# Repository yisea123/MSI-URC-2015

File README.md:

MSI-URC-2015
============
* Clone the repository
* Run gazebo.bash from On-Board if gazebo/ROS/DEM not installed
* Run configure.bash once if cloning to a new place or for first time
* Restart the terminal and type '@urc'

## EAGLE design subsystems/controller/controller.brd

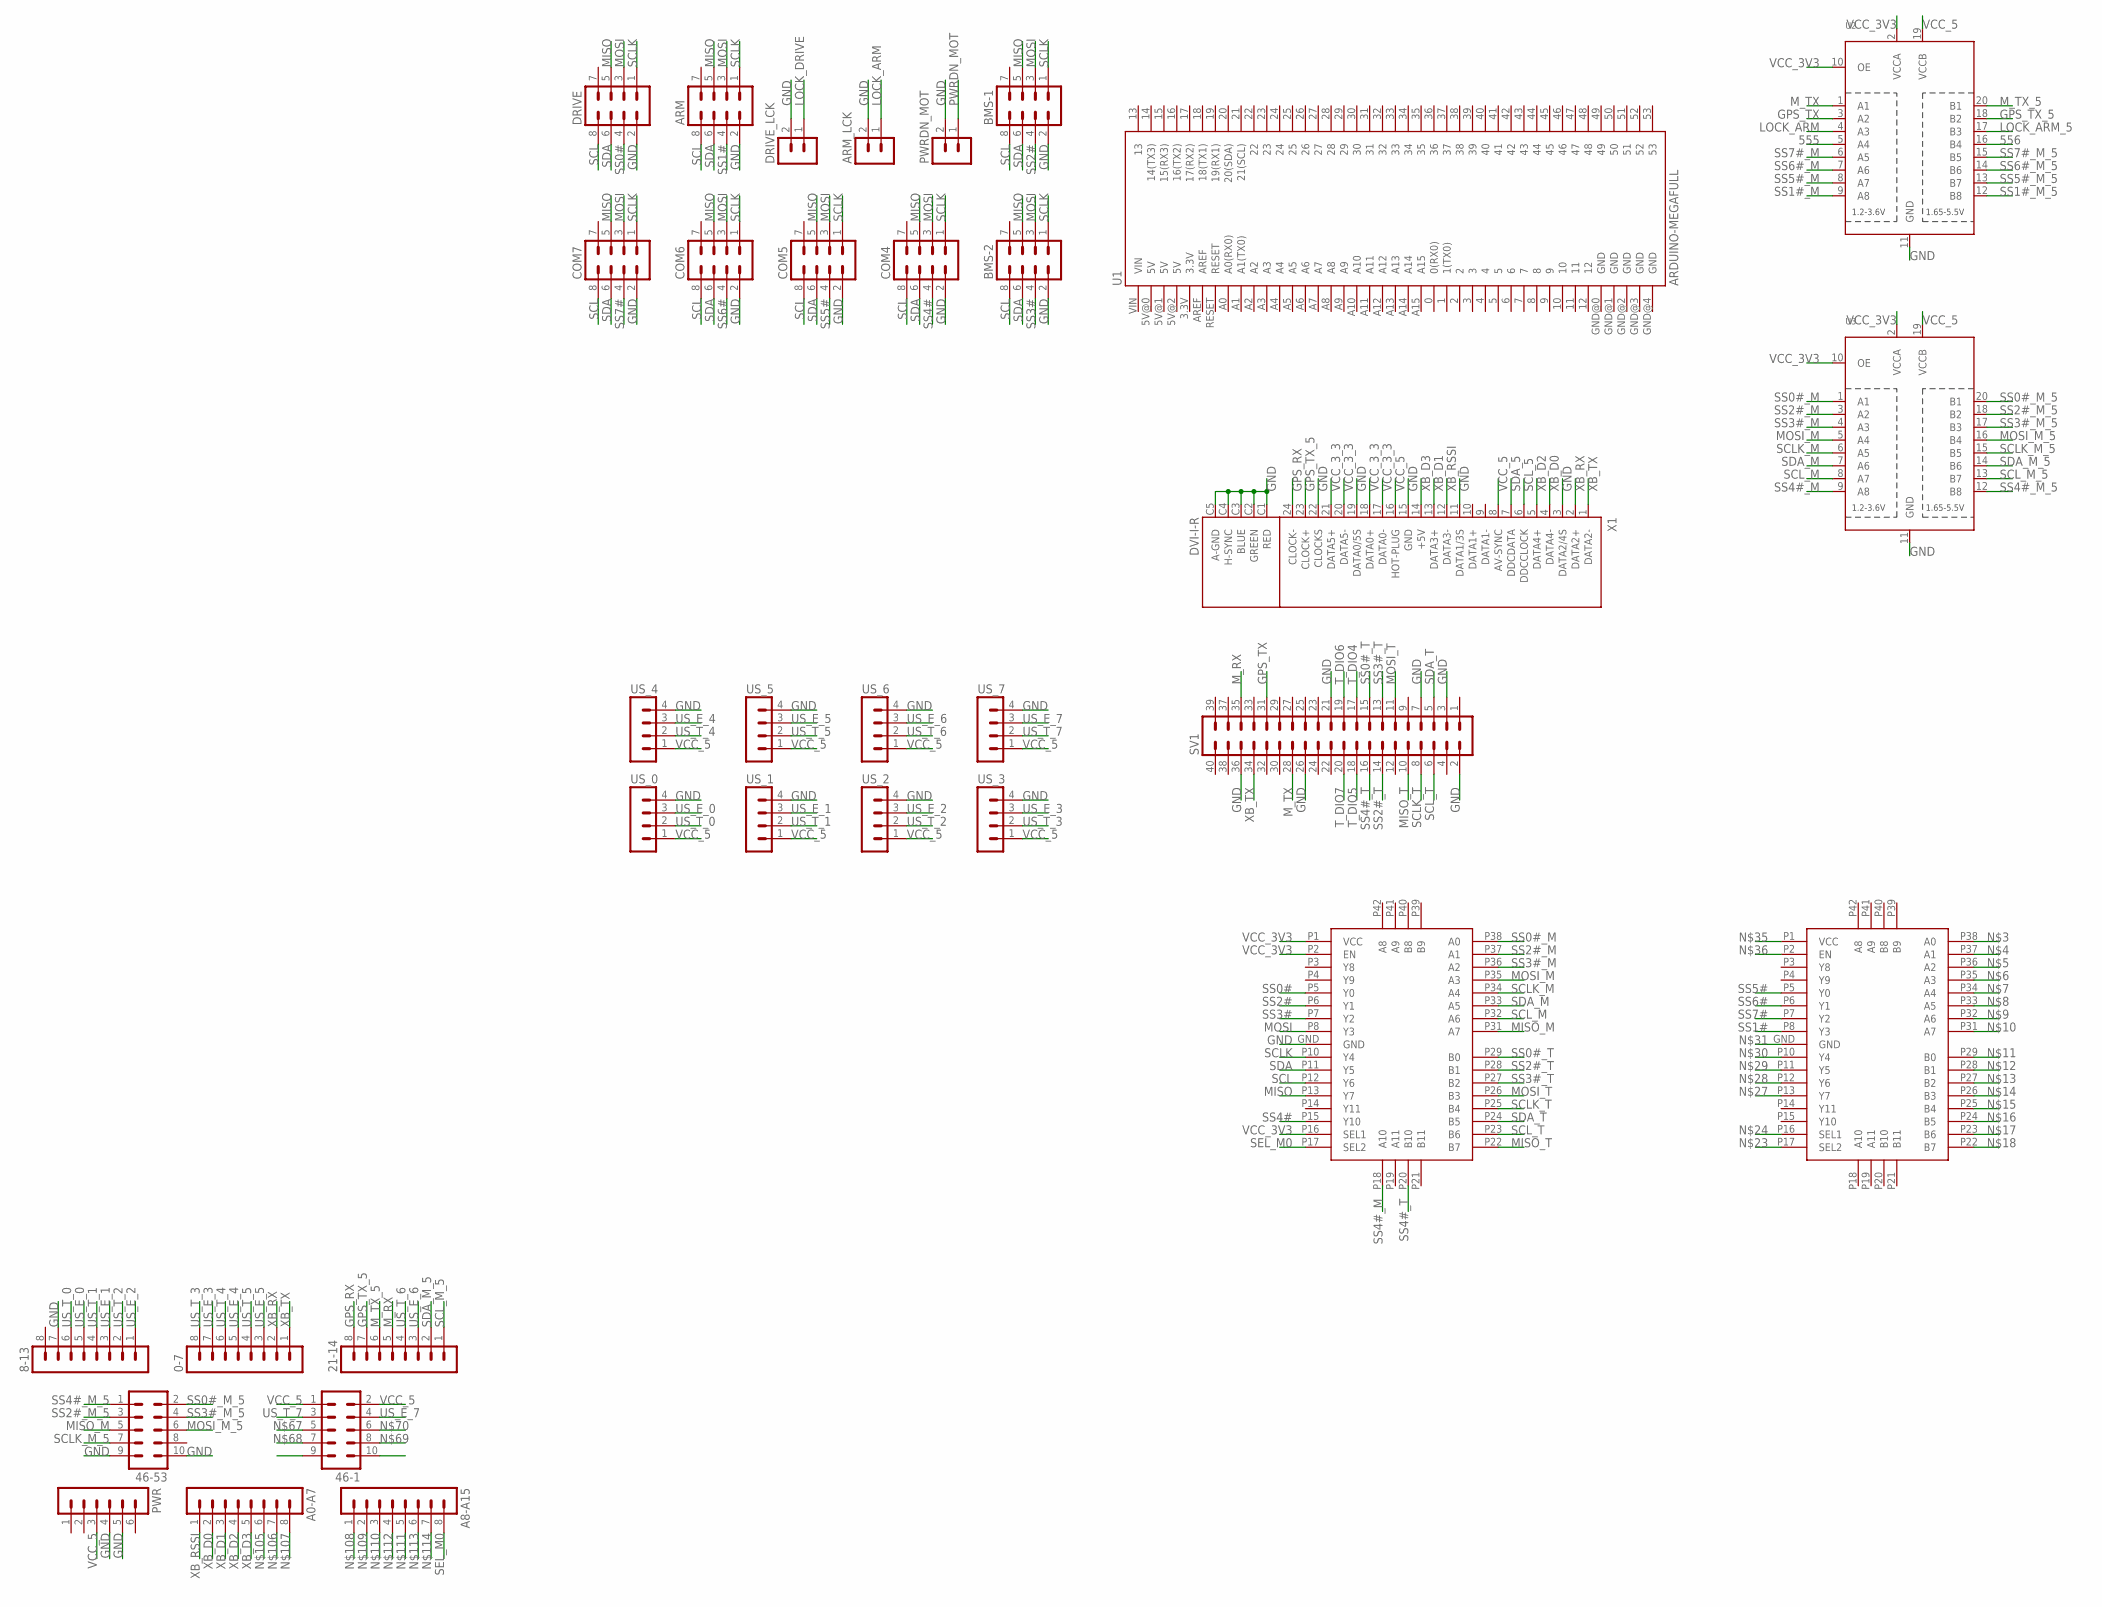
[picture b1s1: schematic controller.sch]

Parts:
0-7, 8-13, 21-14: MA08-1
46-1, 46-53: MA05-2
A0-A7, A8-A15: MA08-1
ARM: MA04-2
ARM_LCK: MA02-1
BMS-1, BMS-2: MA04-2
COM4, COM5, COM6, COM7: MA04-2
DRIVE: MA04-2
DRIVE_LCK: MA02-1
PWR: MA06-1
PWRDN_MOT: MA02-1
SV1: MA20-2
U1: ARDUINO-MEGAFULL; ARDUINO_MEGA
U2, U3: TXB0108PWR; TSSOP20
U$5, U$6: TS3DV642RUA; R-PWQFN-N42
US_0, US_1, US_2, US_3, US_4, US_5, US_6, US_7: MA04-1
X1: DVI-I-R

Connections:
555: U2.5 (A4)
556: U2.16 (B4)
AGND: X1.C6 (AGND)
GND: 8-13.7, 46-53.9, 46-53.10, ARM.2, ARM_LCK.2, BMS-1.2, BMS-2.2, COM4.2, COM5.2, COM6.2, COM7.2, DRIVE.2, DRIVE_LCK.2, PWR.4, PWR.5, PWRDN_MOT.2, SV1.2, SV1.3, SV1.7, SV1.21, SV1.26, SV1.36, U2.11 (GND), U3.11 (GND), U$5.GND, US_0.4, US_1.4, US_2.4, US_3.4, US_4.4, US_5.4, US_6.4, US_7.4, X1.3 (DATA2/4S), X1.11 (DATA1/3S), X1.15 (GND), X1.19 (DATA0/5S), X1.22 (CLOCKS), X1.C1 (RED), X1.C2 (GREEN), X1.C3 (BLUE), X1.C4 (H-SYNC), X1.C5 (A-GND)
GPS_RX: 21-14.8, X1.24 (CLOCK-)
GPS_TX: SV1.31, U2.3 (A2)
GPS_TX_5: 21-14.7, U2.18 (B2), X1.23 (CLOCK+)
LOCK_ARM: ARM_LCK.1, U2.4 (A3)
LOCK_ARM_5: U2.17 (B3)
LOCK_DRIVE: DRIVE_LCK.1
MISO: ARM.5, BMS-1.5, BMS-2.5, COM4.5, COM5.5, COM6.5, COM7.5, DRIVE.5, U$5.P13 (Y7)
MISO_M: 46-53.5, U$5.P31 (A7)
MISO_T: SV1.10, U$5.P22 (B7)
MOSI: ARM.3, BMS-1.3, BMS-2.3, COM4.3, COM5.3, COM6.3, COM7.3, DRIVE.3, U$5.P8 (Y3)
MOSI_M: U3.5 (A4), U$5.P35 (A3)
MOSI_M_5: 46-53.6, U3.16 (B4)
MOSI_T: SV1.11, U$5.P26 (B3)
M_RX: 21-14.5, SV1.35
M_TX: SV1.28, U2.1 (A1)
M_TX_5: 21-14.6, U2.20 (B1)
PWRDN_MOT: PWRDN_MOT.1
SCL: ARM.8, BMS-1.8, BMS-2.8, COM4.8, COM5.8, COM6.8, COM7.8, DRIVE.8, U$5.P12 (Y6)
SCLK: ARM.1, BMS-1.1, BMS-2.1, COM4.1, COM5.1, COM6.1, COM7.1, DRIVE.1, U$5.P10 (Y4)
SCLK_M: U3.6 (A5), U$5.P34 (A4)
SCLK_M_5: 46-53.7, U3.15 (B5)
SCLK_T: SV1.8, U$5.P25 (B4)
SCL_5: X1.6 (DDCCLOCK)
SCL_M: U3.8 (A7), U$5.P32 (A6)
SCL_M_5: 21-14.1, U3.13 (B7)
SCL_T: SV1.6, U$5.P23 (B6)
SDA: ARM.6, BMS-1.6, BMS-2.6, COM4.6, COM5.6, COM6.6, COM7.6, DRIVE.6, U$5.P11 (Y5)
SDA_5: X1.7 (DDCDATA)
SDA_M: U3.7 (A6), U$5.P33 (A5)
SDA_M_5: 21-14.2, U3.14 (B6)
SDA_T: SV1.5, U$5.P24 (B5)
SEL_M0: A8-A15.8, U$5.P17 (SEL2)
SS0#: DRIVE.4, U$5.P5 (Y0)
SS0#_M: U3.1 (A1), U$5.P38 (A0)
SS0#_M_5: 46-53.2, U3.20 (B1)
SS0#_T: SV1.15, U$5.P29 (B0)
SS1#: ARM.4, U$6.P8 (Y3)
SS1#_M: U2.9 (A8)
SS1#_M_5: U2.12 (B8)
SS2#: BMS-1.4, U$5.P6 (Y1)
SS2#_M: U3.3 (A2), U$5.P37 (A1)
SS2#_M_5: 46-53.3, U3.18 (B2)
SS2#_T: SV1.14, U$5.P28 (B1)
SS3#: BMS-2.4, U$5.P7 (Y2)
SS3#_M: U3.4 (A3), U$5.P36 (A2)
SS3#_M_5: 46-53.4, U3.17 (B3)
SS3#_T: SV1.13, U$5.P27 (B2)
SS4#: COM4.4, U$5.P15 (Y10)
SS4#_M: U3.9 (A8), U$5.P18 (A10)
SS4#_M_5: 46-53.1, U3.12 (B8)
SS4#_T: SV1.16, U$5.P20 (B10)
SS5#: COM5.4, U$6.P5 (Y0)
SS5#_M: U2.8 (A7)
SS5#_M_5: U2.13 (B7)
SS6#: COM6.4, U$6.P6 (Y1)
SS6#_M: U2.7 (A6)
SS6#_M_5: U2.14 (B6)
SS7#: COM7.4, U$6.P7 (Y2)
SS7#_M: U2.6 (A5)
SS7#_M_5: U2.15 (B5)
T_DIO4: SV1.17
T_DIO5: SV1.18
T_DIO6: SV1.19
T_DIO7: SV1.20
US_E_0: 8-13.5, US_0.3
US_E_1: 8-13.3, US_1.3
US_E_2: 8-13.1, US_2.3
US_E_3: 0-7.7, US_3.3
US_E_4: 0-7.5, US_4.3
US_E_5: 0-7.3, US_5.3
US_E_6: 21-14.3, US_6.3
US_E_7: 46-1.4, US_7.3
US_T_0: 8-13.6, US_0.2
US_T_1: 8-13.4, US_1.2
US_T_2: 8-13.2, US_2.2
US_T_3: 0-7.8, US_3.2
US_T_4: 0-7.6, US_4.2
US_T_5: 0-7.4, US_5.2
US_T_6: 21-14.4, US_6.2
US_T_7: 46-1.3, US_7.2
VCC_3V3: U2.2 (VCCA), U2.10 (OE), U3.2 (VCCA), U3.10 (OE), U$5.P1 (VCC), U$5.P2 (EN), U$5.P16 (SEL1)
VCC_3_3: X1.17 (DATA0-), X1.18 (DATA0+), X1.20 (DATA5-), X1.21 (DATA5+)
VCC_5: 46-1.1, 46-1.2, PWR.3, U2.19 (VCCB), U3.19 (VCCB), US_0.1, US_1.1, US_2.1, US_3.1, US_4.1, US_5.1, US_6.1, US_7.1, X1.8 (AV-SYNC), X1.16 (HOT-PLUG)
XB_D0: A0-A7.2, X1.4 (DATA4-)
XB_D1: A0-A7.3, X1.13 (DATA3+)
XB_D2: A0-A7.4, X1.5 (DATA4+)
XB_D3: A0-A7.5, X1.14 (+5V)
XB_RSSI: A0-A7.1, X1.12 (DATA3-)
XB_RX: 0-7.2, X1.2 (DATA2+)
XB_TX: 0-7.1, SV1.34, X1.1 (DATA2-)

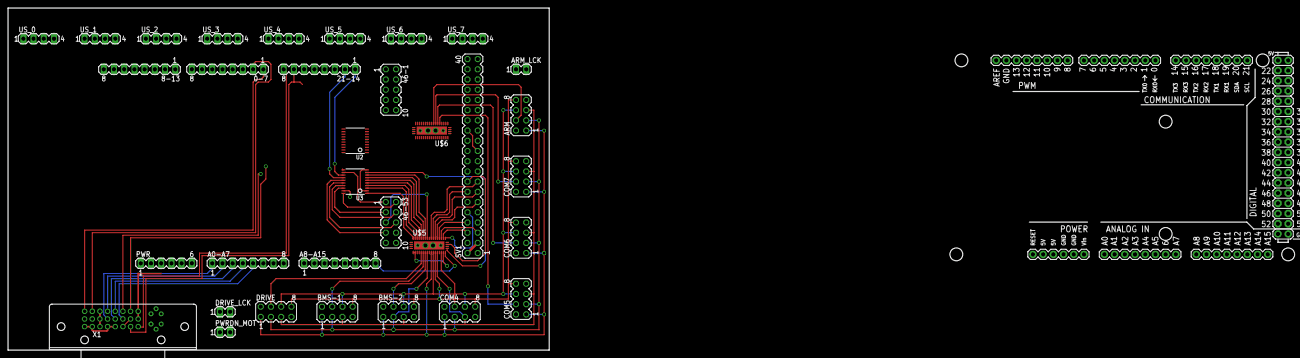
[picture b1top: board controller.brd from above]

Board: 2 copper layers, 134.6 x 85.1 mm, 34 parts (0 on the bottom side), 74 nets.

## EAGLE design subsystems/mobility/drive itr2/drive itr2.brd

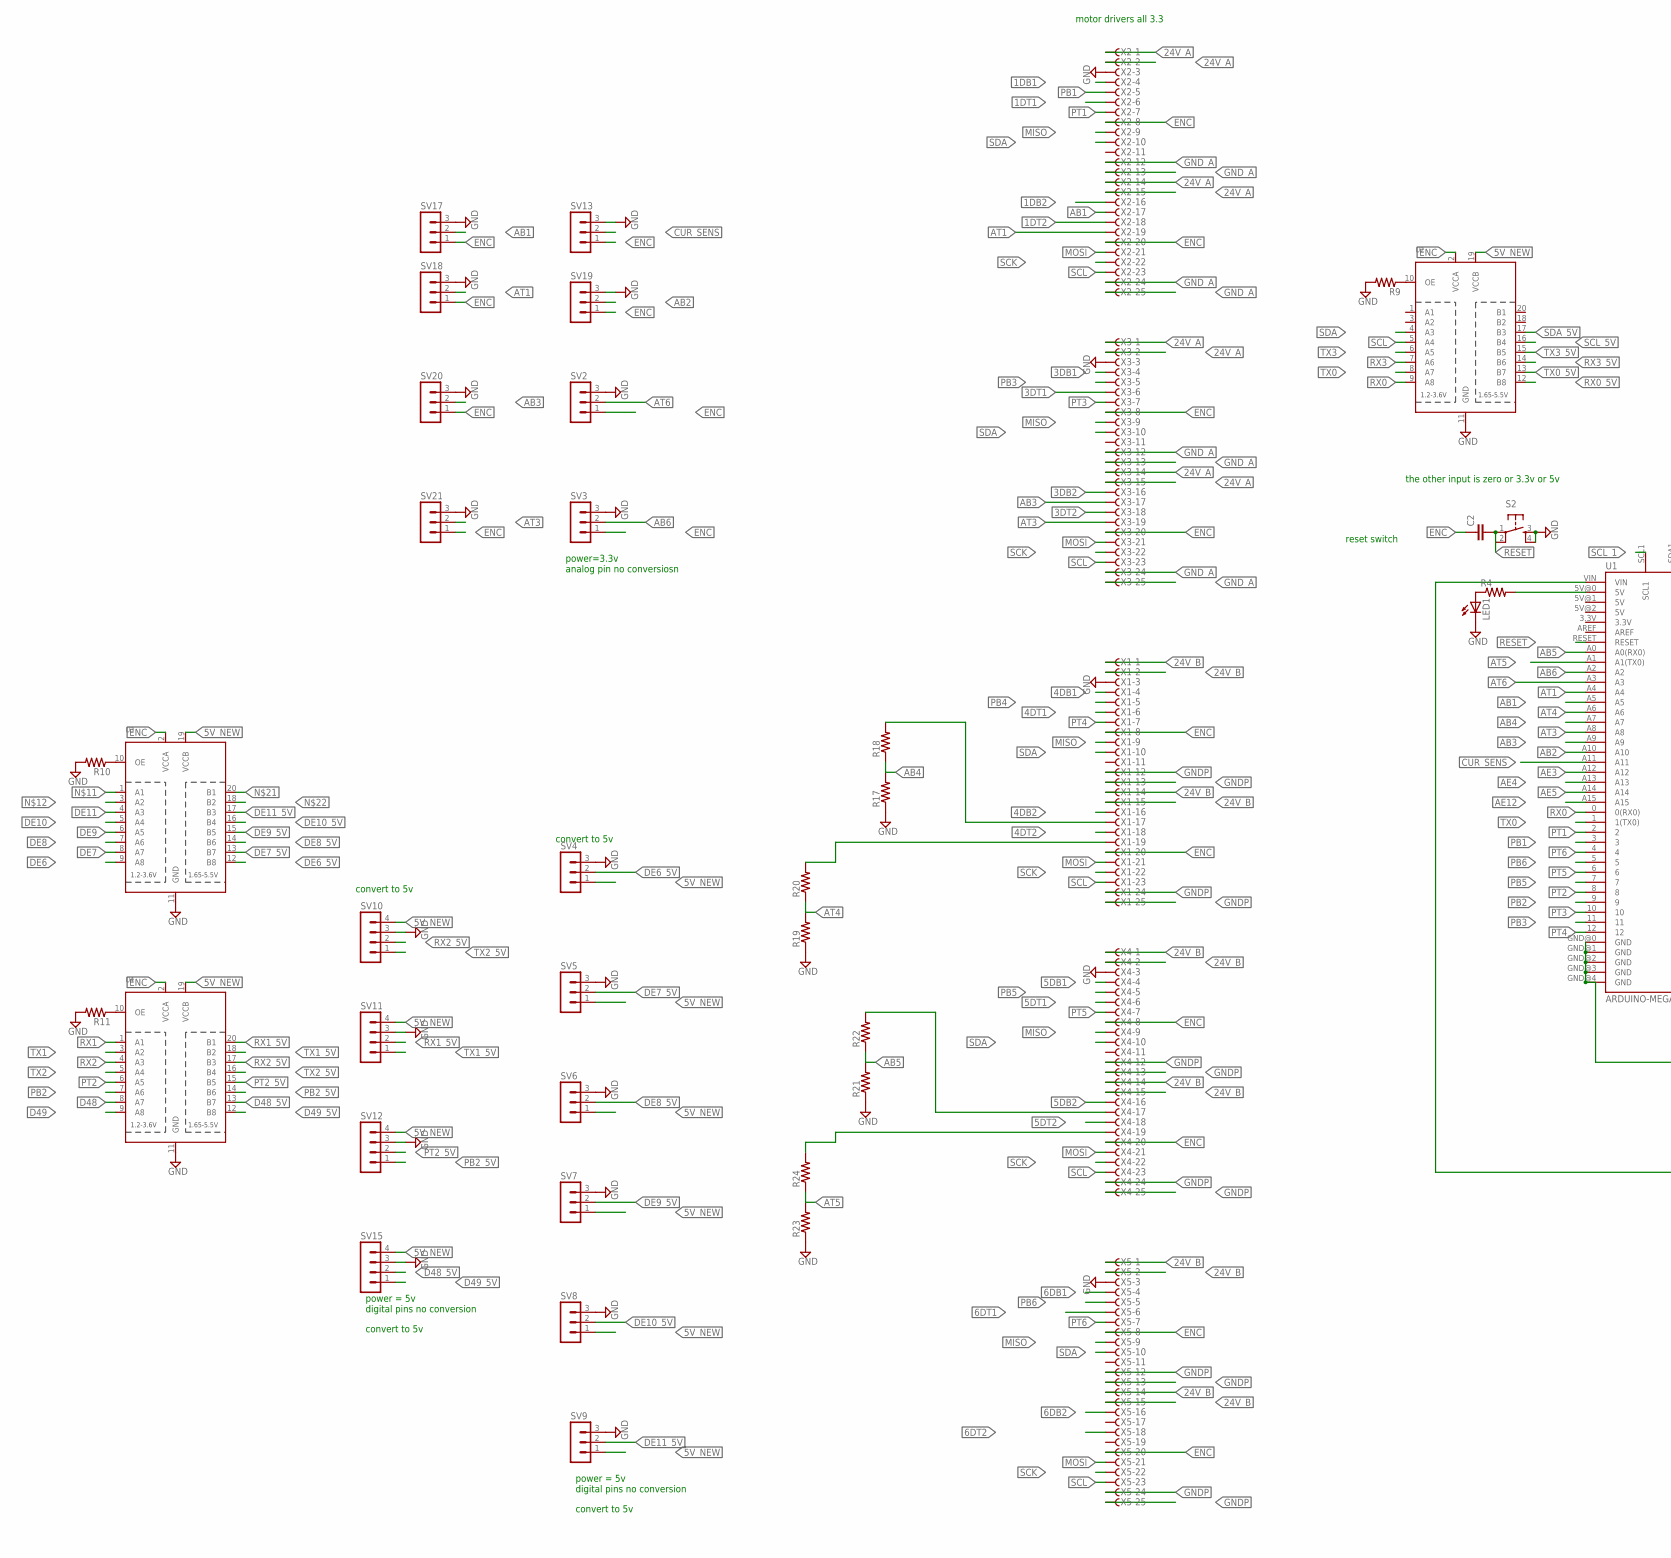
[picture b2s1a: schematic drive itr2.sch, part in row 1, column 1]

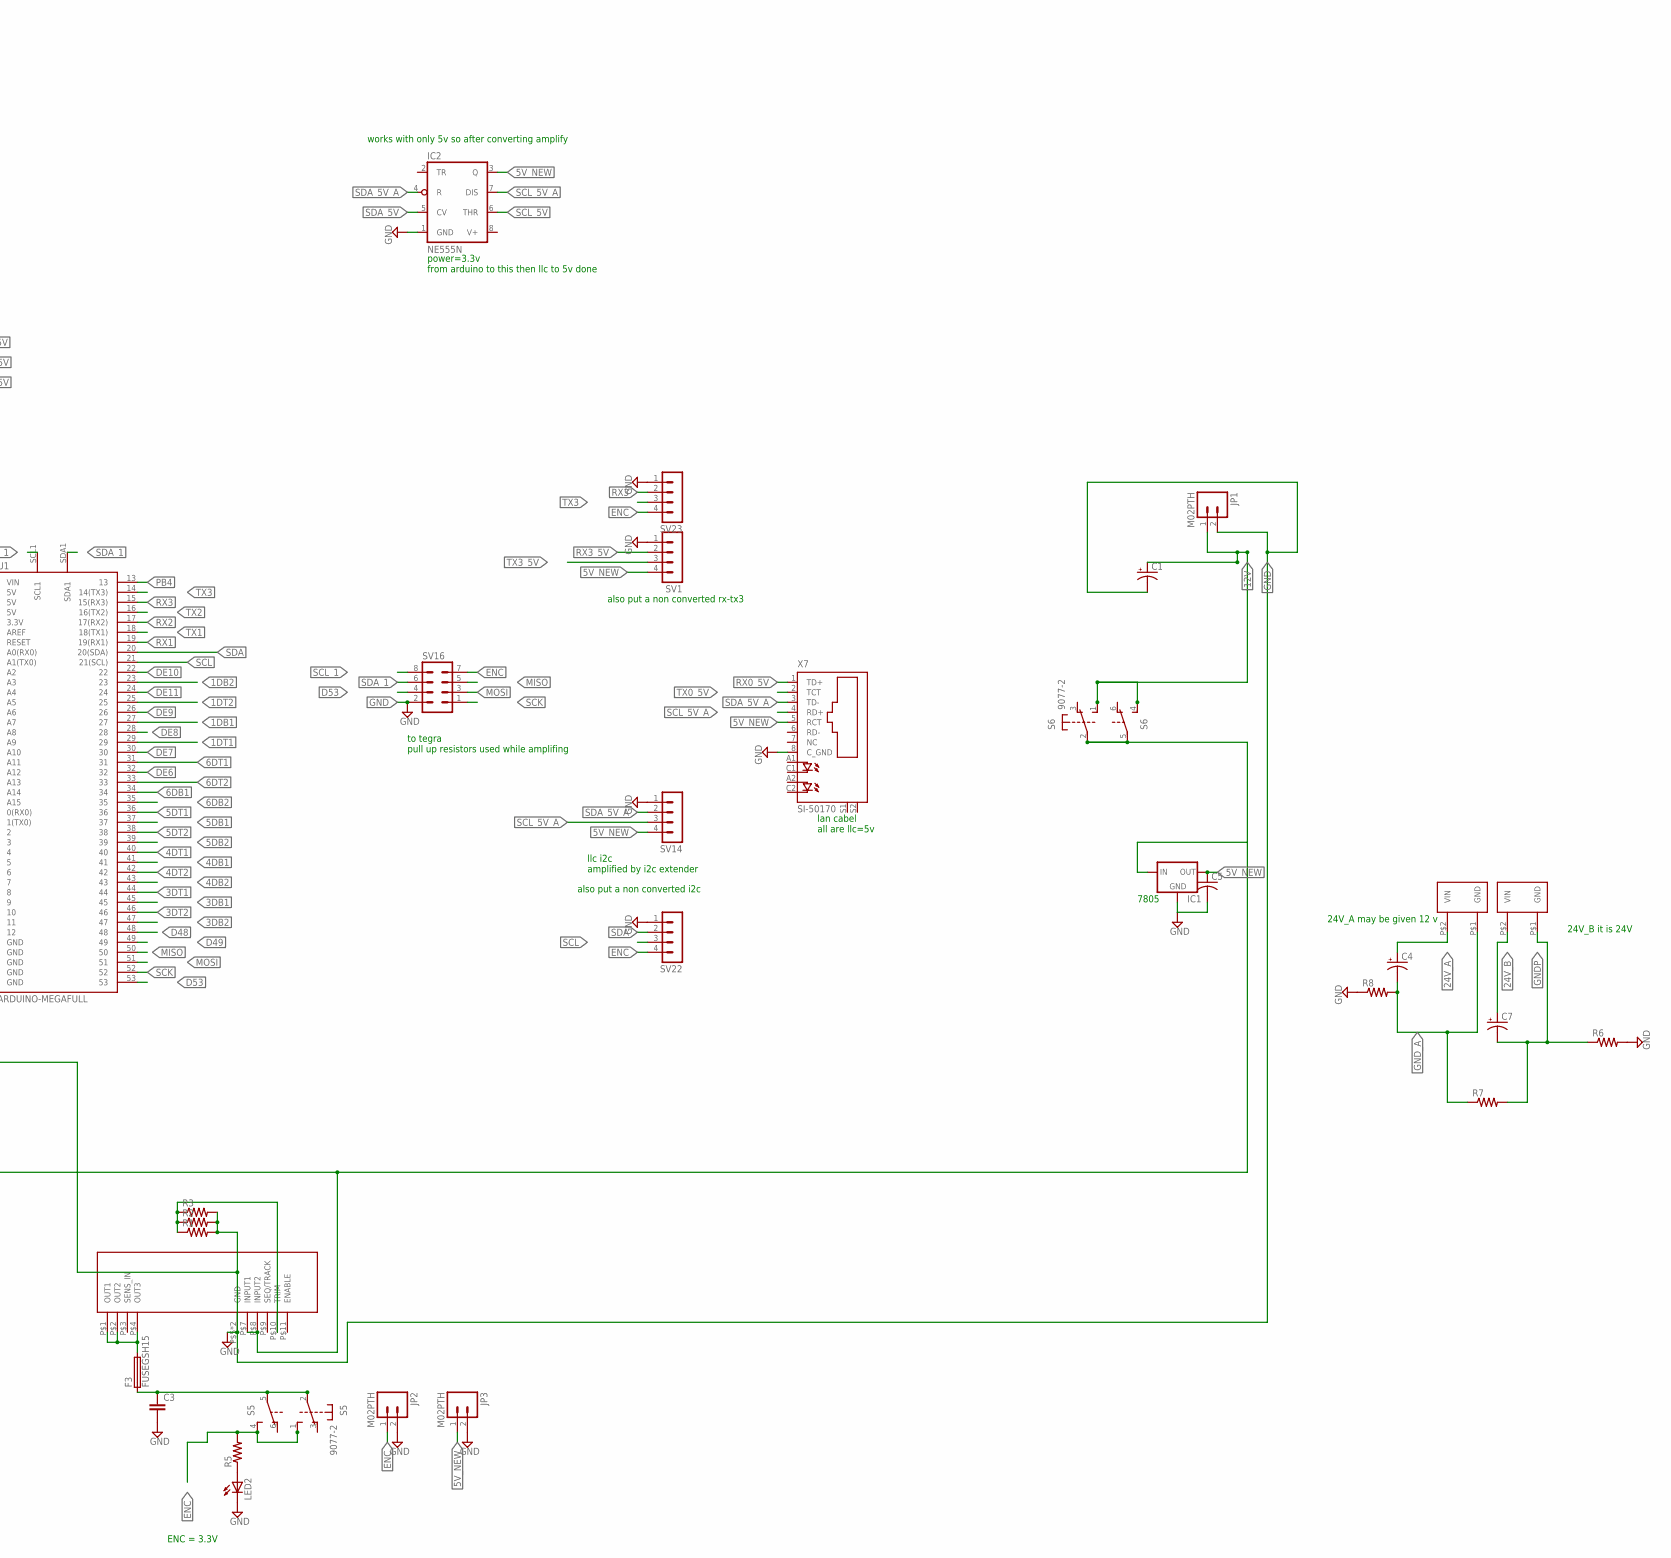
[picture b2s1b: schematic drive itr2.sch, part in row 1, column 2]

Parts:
C1, C4, C7: CPOL-USE2.5-5; E2,5-5
C2: C2,5-3; C2.5-3
C3: C2.5/2; C2.5-2
C5: C-US025-030X050; C025-030X050
F3: FUSEGSH15; GSH15
IC1: V_REG_78XX-TO-220; TO-220-ALT
IC2: NE555N; DIL08-ROUND
JP1, JP2, JP3: M02PTH; 1X02
LED1, LED2: LED3MM
R1, R2, R3, R4, R5, R6, R7, R8, R9, R10, R11, R17, R18, R19, R20, R21, R22, R23, R24: R-US_0207/10; 0207/10
S2: TAC_SWITCHSMD; TACTILE-SWITCH-SMD
S5, S6: 9077-2
SV1, SV10, SV11, SV12, SV14, SV15, SV22, SV23: MA04-1
SV2, SV3, SV4, SV5, SV6, SV7, SV8, SV9, SV13, SV17, SV18, SV19, SV20, SV21: MA03-1
SV16: MA04-2
U1: ARDUINO-MEGAFULL; ARDUINO_MEGA
U2, U3, U4: TXB0108PWR; TSSOP20
U$7: VREG-MURATA; VREG
U$8, U$9: POW_HOLE
X1, X2, X3, X4, X5: F25HPS; F25HP
X7: SI-50170

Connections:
1DB1: U1.27, X2.4
1DB2: U1.23, X2.16
1DT1: U1.29, X2.6
1DT2: U1.25, X2.18
3DB1: U1.45, X3.4
3DB2: U1.47, X3.16
3DT1: U1.44, X3.6
3DT2: U1.46, X3.18
4DB1: U1.41, X1.4
4DB2: U1.43, X1.16
4DT1: U1.40, X1.6
4DT2: U1.42, X1.18
5DB1: U1.37, X4.4
5DB2: U1.39, X4.16
5DT1: U1.36, X4.6
5DT2: U1.38, X4.18
5V_NEW: C5.1, IC1.OUT, IC2.3 (Q), JP3.1, SV1.4, SV4.1, SV5.1, SV6.1, SV7.1, SV8.1, SV9.1, SV10.4, SV11.4, SV12.4, SV14.4, SV15.4, U2.19 (VCCB), U3.19 (VCCB), U4.19 (VCCB), X7.5 (RCT)
6DB1: U1.34, X5.4
6DB2: U1.35, X5.16
6DT1: U1.31, X5.6
6DT2: U1.33, X5.18
12V: C1.+, JP1.1, S6.1 (S), S6.4 (S)
24V_A: C4.+, U$9.P$2 (VIN), X2.1, X2.2, X2.14, X2.15, X3.1, X3.2, X3.14, X3.15
24V_B: C7.+, U$8.P$2 (VIN), X1.1, X1.2, X1.14, X1.15, X4.1, X4.2, X4.14, X4.15, X5.1, X5.2, X5.14, X5.15
AB1: SV17.2, U1.A5, X2.17
AB2: SV19.2, U1.A10
AB3: SV20.2, U1.A9, X3.17
AB4: R17.2, R18.1, U1.A7
AB5: R21.2, R22.1, U1.A0 (A0(RX0))
AB6: SV3.2, U1.A2
AE3: U1.A12
AE4: U1.A13
AE5: U1.A14
AE12: U1.A15
AT1: SV18.2, U1.A4
AT3: SV21.2, U1.A8, X3.19
AT4: R19.2, R20.1, U1.A6
AT5: R23.2, R24.1, U1.A1 (A1(TX0))
AT6: SV2.2, U1.A3
CONN: C3.1, F3.1, S5.2, S5.5
CUR_SENS: SV13.2, U1.A11
D48: U1.48, U4.8 (A7)
D48_5V: SV15.2, U4.13 (B7)
D49: U1.49, U4.9 (A8)
D49_5V: SV15.1, U4.12 (B8)
D53: SV16.4, U1.53
DE6: U1.32, U3.9 (A8)
DE6_5V: SV4.2, U3.12 (B8)
DE7: U1.30, U3.8 (A7)
DE7_5V: SV5.2, U3.13 (B7)
DE8: U1.28, U3.7 (A6)
DE8_5V: SV6.2, U3.14 (B6)
DE9: U1.26, U3.6 (A5)
DE9_5V: SV7.2, U3.15 (B5)
DE10: U1.22, U3.5 (A4)
DE10_5V: SV8.2, U3.16 (B4)
DE11: U1.24, U3.4 (A3)
DE11_5V: SV9.2, U3.17 (B3)
ENC: C2.1, JP2.1, R5.2, S5.1 (S), S5.4 (S), SV2.1, SV3.1, SV13.1, SV16.7, SV17.1, SV18.1, SV19.1, SV20.1, SV21.1, SV22.4, SV23.4, U2.2 (VCCA), U3.2 (VCCA), U4.2 (VCCA), X1.8, X1.20, X2.8, X2.20, X3.8, X3.20, X4.8, X4.20, X5.8, X5.20
GND: C1.-, C3.2, C5.2, IC1.GND, IC2.1 (GND), JP1.2, JP2.2, JP3.2, LED1.K (C), LED2.K (C), R1.2, R2.2, R3.2, R6.2, R8.1, R9.2, R10.2, R11.2, R17.1, R19.1, R21.1, R23.1, S2.3, S2.4, SV1.1, SV2.3, SV3.3, SV4.3, SV5.3, SV6.3, SV7.3, SV8.3, SV9.3, SV10.3, SV11.3, SV12.3, SV13.3, SV14.1, SV15.3, SV16.2, SV17.3, SV18.3, SV19.3, SV20.3, SV21.3, SV22.1, SV23.1, U1.GND@0 (GND), U1.GND@1 (GND), U1.GND@2 (GND), U1.GND@3 (GND), U1.GND@4 (GND), U2.11 (GND), U3.11 (GND), U4.11 (GND), U$7.P$5 (GND), U$7.P$6 (GND), X1.3, X2.3, X3.3, X4.3, X5.3, X7.8 (C_GND)
GNDP: C7.-, R6.1, R7.2, U$8.P$1 (GND), X1.12, X1.13, X1.24, X1.25, X4.12, X4.13, X4.24, X4.25, X5.12, X5.13, X5.24, X5.25
GND_A: C4.-, R7.1, R8.2, U$9.P$1 (GND), X2.12, X2.13, X2.24, X2.25, X3.12, X3.13, X3.24, X3.25
MISO: SV16.5, U1.50, X1.9, X2.9, X3.9, X4.9, X5.9
MOSI: SV16.3, U1.51, X1.21, X2.21, X3.21, X4.21, X5.21
unnamed: R9.1, U2.10 (OE)
unnamed: R10.1, U3.10 (OE)
unnamed: R11.1, U4.10 (OE)
unnamed: LED2.A, R5.1
unnamed: LED1.A, R4.1
unnamed: R4.2, U1.5V@0 (5V)
unnamed: F3.2, U$7.P$1 (OUT1), U$7.P$2 (OUT2), U$7.P$4 (OUT3)
unnamed: IC1.IN, S6.2, S6.5, U1.VIN, U$7.P$7 (INPUT1), U$7.P$8 (INPUT2)
unnamed: R18.2, X1.17
unnamed: R20.2, X1.19
unnamed: R22.2, X4.17
unnamed: R24.2, X4.19
unnamed: R1.1, R2.1, R3.1, U$7.P$10 (TRIM)
PB1: U1.3, X2.5
PB2: U1.9, U4.7 (A6)
PB2_5V: SV12.1, U4.14 (B6)
PB3: U1.11, X3.5
PB4: U1.13, X1.5
PB5: U1.7, X4.5
PB6: U1.5, X5.5
PT1: U1.2, X2.7
PT2: U1.8, U4.6 (A5)
PT2_5V: SV12.2, U4.15 (B5)
PT3: U1.10, X3.7
PT4: U1.12, X1.7
PT5: U1.6, X4.7
PT6: U1.4, X5.7
RESET: C2.2, S2.1, S2.2, U1.RESET
RX0: U1.0 (0(RX0)), U2.9 (A8)
RX0_5V: U2.12 (B8), X7.1 (TD+)
RX1: U1.19 (19(RX1)), U4.1 (A1)
RX1_5V: SV11.2, U4.20 (B1)
RX2: U1.17 (17(RX2)), U4.4 (A3)
RX2_5V: SV10.2, U4.17 (B3)
RX3: SV23.2, U1.15 (15(RX3)), U2.7 (A6)
RX3_5V: SV1.2, U2.14 (B6)
SCK: SV16.1, U1.52, X1.22, X2.22, X3.22, X4.22, X5.22
SCL: SV22.3, U1.21 (21(SCL)), U2.5 (A4), X1.23, X2.23, X3.23, X4.23, X5.23
SCL_1: SV16.8, U1.SCL1
SCL_5V: IC2.6 (THR), U2.16 (B4)
SCL_5V_A: IC2.7 (DIS), SV14.3, X7.4 (RD+)
SDA: SV22.2, U1.20 (20(SDA)), U2.4 (A3), X1.10, X2.10, X3.10, X4.10, X5.10
SDA_1: SV16.6, U1.SDA1
SDA_5V: IC2.5 (CV), U2.17 (B3)
SDA_5V_A: IC2.4 (R), SV14.2, X7.3 (TD-)
TX0: U1.1 (1(TX0)), U2.8 (A7)
TX0_5V: U2.13 (B7), X7.2 (TCT)
TX1: U1.18 (18(TX1)), U4.3 (A2)
TX1_5V: SV11.1, U4.18 (B2)
TX2: U1.16 (16(TX2)), U4.5 (A4)
TX2_5V: SV10.1, U4.16 (B4)
TX3: SV23.3, U1.14 (14(TX3)), U2.6 (A5)
TX3_5V: SV1.3, U2.15 (B5)
V+: IC2.8 (V+)

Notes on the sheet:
power = 5v digital pins no conversion
power=3.3v analog pin no conversiosn
power=3.3v from arduino to this then llc to 5v done
llc i2c amplified by i2c extender
lan cabel all are llc=5v
24V_A may be given 12 v
24V_B it is 24V
ENC = 3.3V
to tegra pull up resistors used while amplifing
reset switch
7805
the other input is zero or 3.3v or 5v
motor drivers all 3.3
works with only 5v so after converting amplify
also put a non converted rx-tx3
also put a non converted i2c
convert to 5v

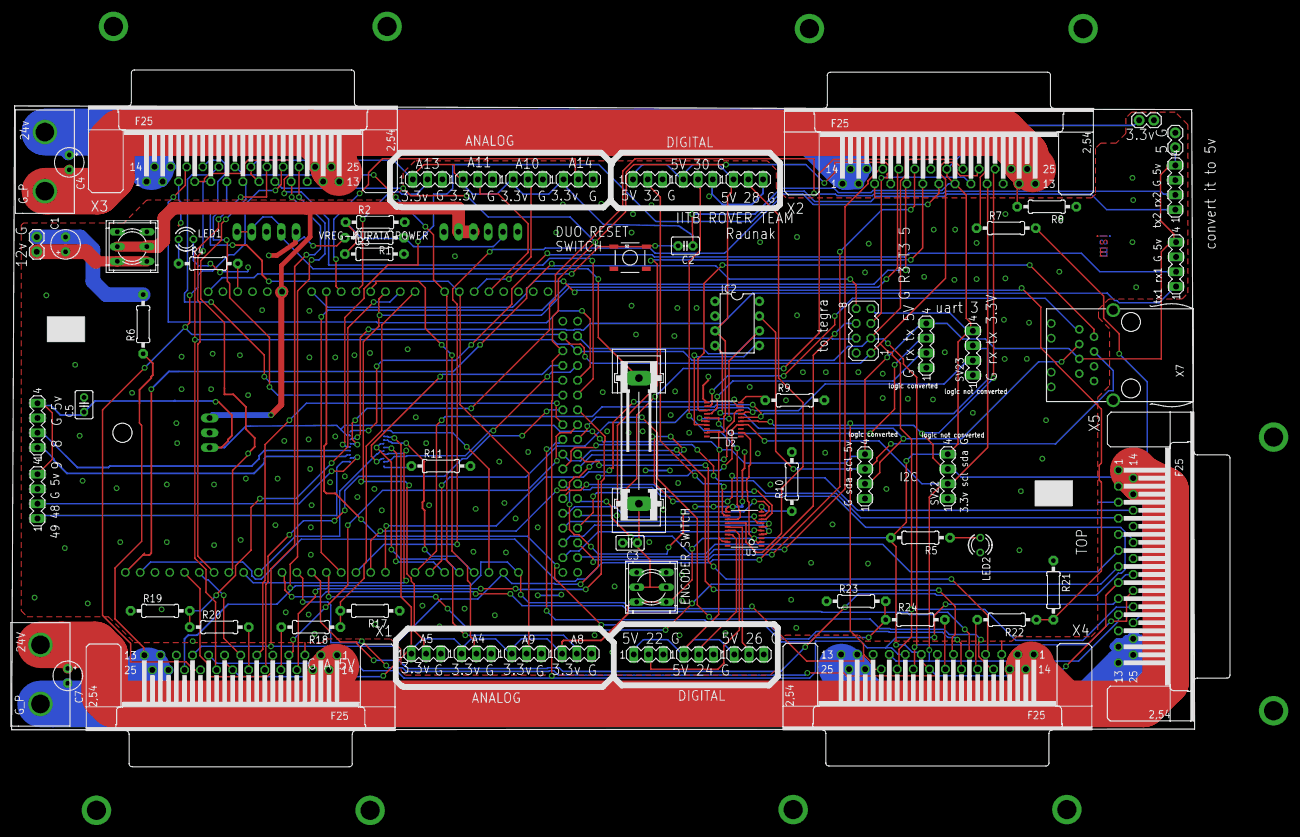
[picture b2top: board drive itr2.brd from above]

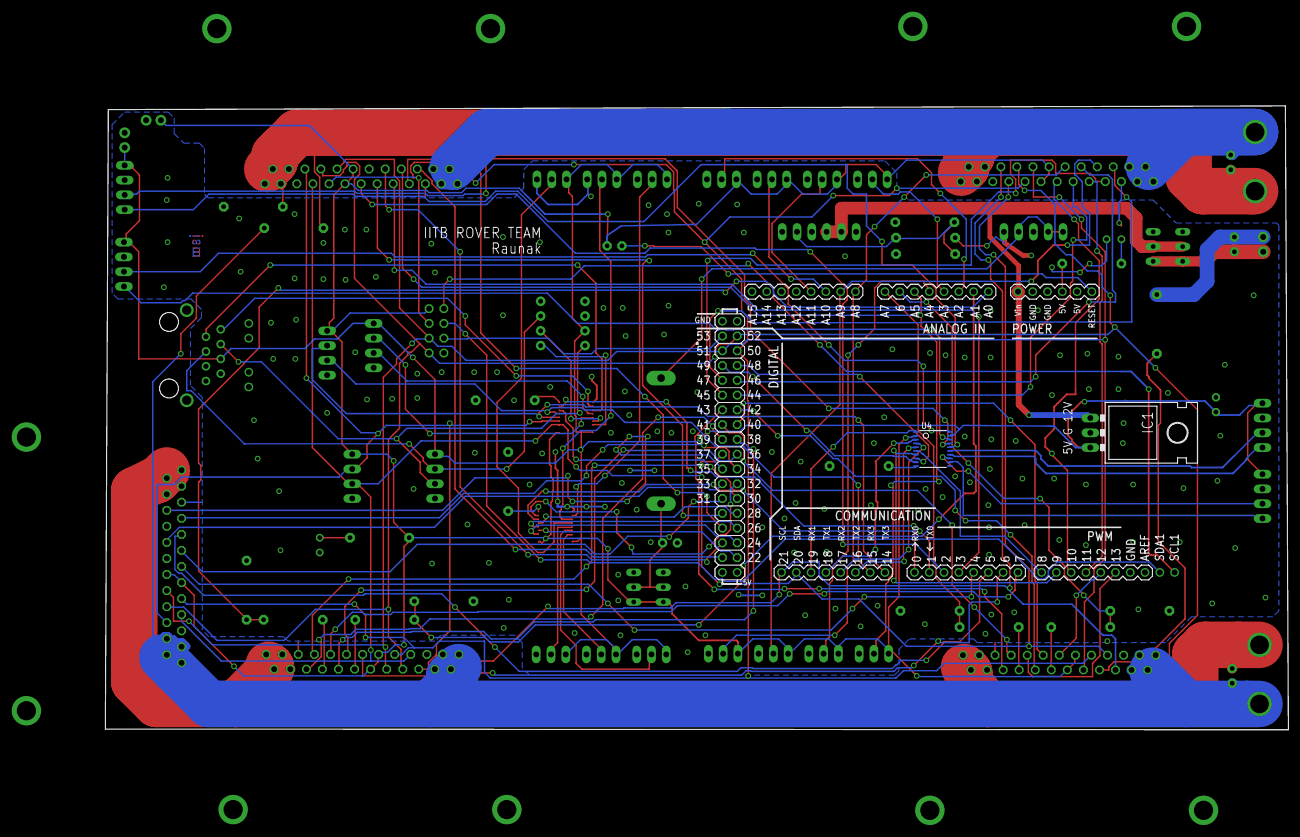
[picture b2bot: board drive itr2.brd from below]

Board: 2 copper layers, 203.3 x 107.2 mm, 74 parts (3 on the bottom side), 113 nets.

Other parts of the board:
U$1, U$2: MSI

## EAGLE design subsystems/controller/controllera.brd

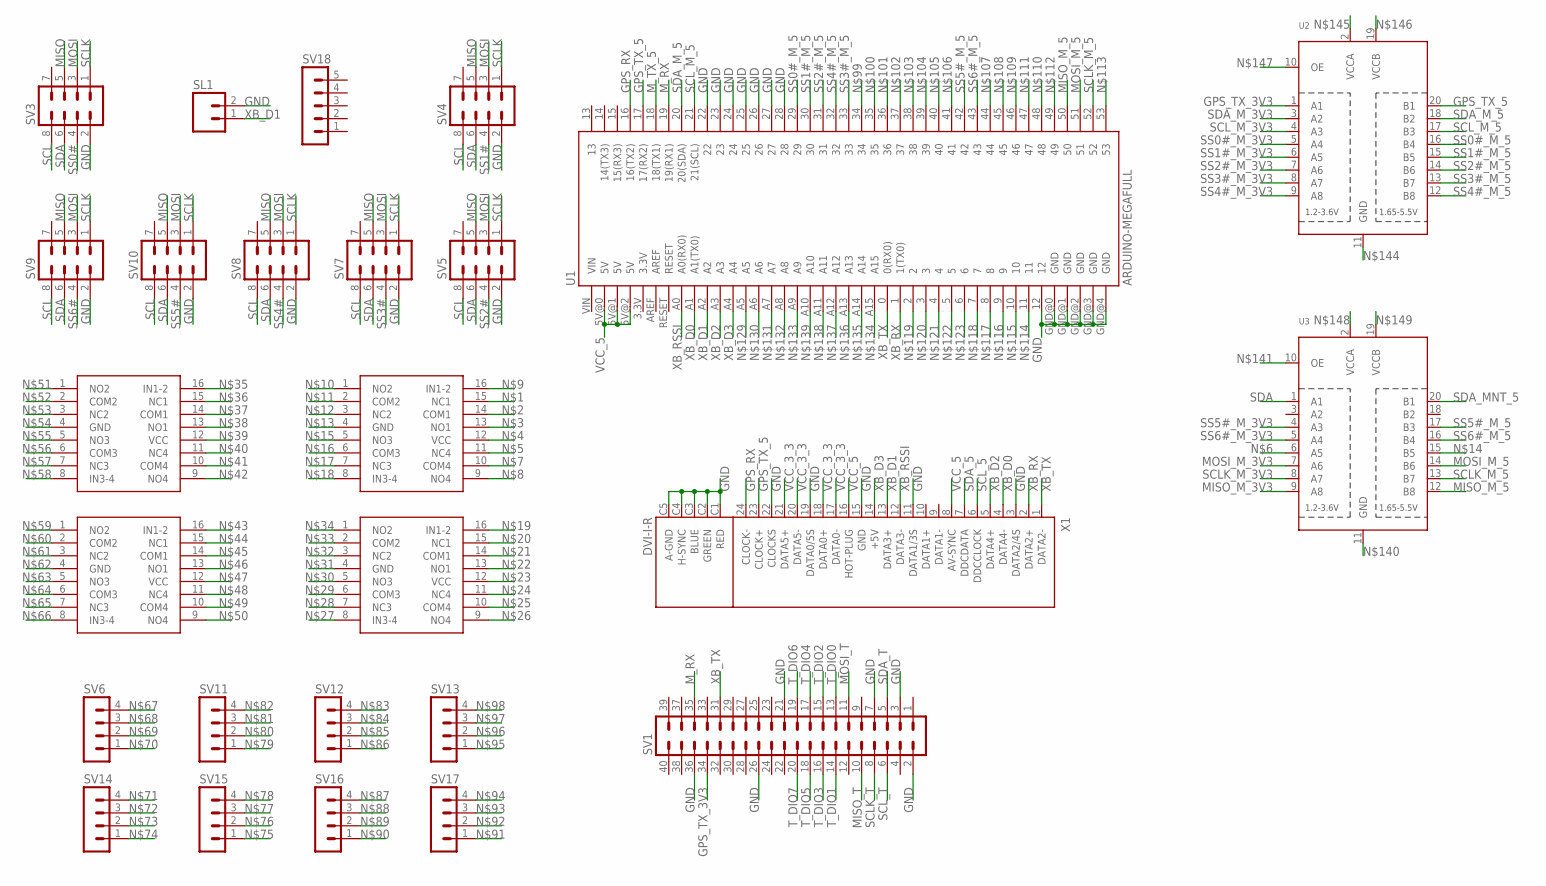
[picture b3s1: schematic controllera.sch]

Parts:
SL1: MA02; 02PA
SV1: MA20-2
SV3, SV4, SV5, SV7, SV8, SV9, SV10: MA04-2
SV6, SV11, SV12, SV13, SV14, SV15, SV16, SV17: MA04-1
SV18: MA05-1
U1: ARDUINO-MEGAFULL; ARDUINO_MEGA
U2, U3: TXB0108PWR; TSSOP20
U$1, U$2, U$3, U$4: TS3A44159PWR; R-PDSO-G16
X1: DVI-I-R

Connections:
AGND: X1.C6 (AGND)
GND: SL1.2, SV1.2, SV1.3, SV1.7, SV1.21, SV1.26, SV1.36, SV3.2, SV4.2, SV5.2, SV7.2, SV8.2, SV9.2, SV10.2, U1.12, U1.22, U1.23, U1.24, U1.25, U1.26, U1.27, U1.28, U1.GND@0 (GND), U1.GND@1 (GND), U1.GND@2 (GND), U1.GND@3 (GND), U1.GND@4 (GND), X1.3 (DATA2/4S), X1.11 (DATA1/3S), X1.15 (GND), X1.19 (DATA0/5S), X1.22 (CLOCKS), X1.C1 (RED), X1.C2 (GREEN), X1.C3 (BLUE), X1.C4 (H-SYNC), X1.C5 (A-GND)
GPS_RX: U1.16 (16(TX2)), X1.24 (CLOCK-)
GPS_TX_3V3: SV1.34, U2.1 (A1)
GPS_TX_5: U1.17 (17(RX2)), U2.20 (B1), X1.23 (CLOCK+)
MISO: SV3.5, SV4.5, SV5.5, SV7.5, SV8.5, SV9.5, SV10.5
MISO_M_3V3: U3.9 (A8)
MISO_M_5: U1.50, U3.12 (B8)
MISO_T: SV1.10
MOSI: SV3.3, SV4.3, SV5.3, SV7.3, SV8.3, SV9.3, SV10.3
MOSI_M_3V3: U3.7 (A6)
MOSI_M_5: U1.51, U3.14 (B6)
MOSI_T: SV1.11
M_RX: SV1.35, U1.19 (19(RX1))
M_TX_5: U1.18 (18(TX1))
SCL: SV3.8, SV4.8, SV5.8, SV7.8, SV8.8, SV9.8, SV10.8
SCLK: SV3.1, SV4.1, SV5.1, SV7.1, SV8.1, SV9.1, SV10.1
SCLK_M_3V3: U3.8 (A7)
SCLK_M_5: U1.52, U3.13 (B7)
SCLK_T: SV1.8
SCL_5: X1.6 (DDCCLOCK)
SCL_M_3V3: U2.4 (A3)
SCL_M_5: U1.21 (21(SCL)), U2.17 (B3)
SCL_T: SV1.6
SDA: SV3.6, SV4.6, SV5.6, SV7.6, SV8.6, SV9.6, SV10.6, U3.1 (A1)
SDA_5: X1.7 (DDCDATA)
SDA_MNT_5: U3.20 (B1)
SDA_M_3V3: U2.3 (A2)
SDA_M_5: U1.20 (20(SDA)), U2.18 (B2)
SDA_T: SV1.5
SS0#: SV3.4
SS0#_M_3V3: U2.5 (A4)
SS0#_M_5: U1.29, U2.16 (B4)
SS1#: SV4.4
SS1#_M_3V3: U2.6 (A5)
SS1#_M_5: U1.30, U2.15 (B5)
SS2#: SV5.4
SS2#_M_3V3: U2.7 (A6)
SS2#_M_5: U1.31, U2.14 (B6)
SS3#: SV7.4
SS3#_M_3V3: U2.8 (A7)
SS3#_M_5: U1.33, U2.13 (B7)
SS4#: SV8.4
SS4#_M_3V3: U2.9 (A8)
SS4#_M_5: U1.32, U2.12 (B8)
SS5#: SV10.4
SS5#_M_3V3: U3.4 (A3)
SS5#_M_5: U1.42, U3.17 (B3)
SS6#: SV9.4
SS6#_M_3V3: U3.5 (A4)
SS6#_M_5: U1.43, U3.16 (B4)
T_DIO0: SV1.13
T_DIO1: SV1.14
T_DIO2: SV1.15
T_DIO3: SV1.16
T_DIO4: SV1.17
T_DIO5: SV1.18
T_DIO6: SV1.19
T_DIO7: SV1.20
VCC_3_3: X1.17 (DATA0-), X1.18 (DATA0+), X1.20 (DATA5-), X1.21 (DATA5+)
VCC_5: U1.5V@0 (5V), U1.5V@1 (5V), U1.5V@2 (5V), X1.8 (AV-SYNC), X1.16 (HOT-PLUG)
XB_D0: U1.A1 (A1(TX0)), X1.4 (DATA4-)
XB_D1: SL1.1, U1.A2, X1.13 (DATA3+)
XB_D2: U1.A3, X1.5 (DATA4+)
XB_D3: U1.A4, X1.14 (+5V)
XB_RSSI: U1.A0 (A0(RX0)), X1.12 (DATA3-)
XB_RX: U1.1 (1(TX0)), X1.2 (DATA2+)
XB_TX: SV1.31, U1.0 (0(RX0)), X1.1 (DATA2-)

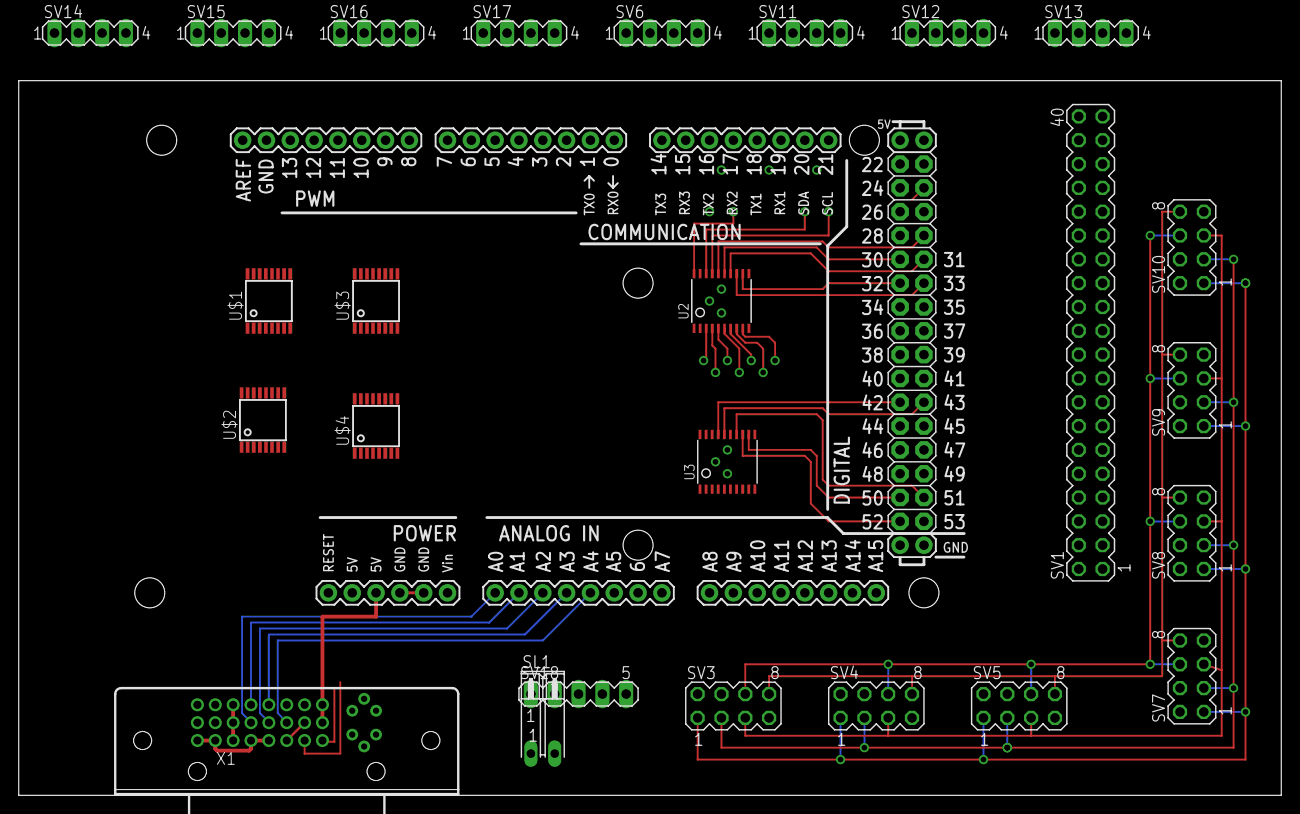
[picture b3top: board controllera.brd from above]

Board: 2 copper layers, 134.6 x 76.2 mm, 26 parts (0 on the bottom side), 31 nets.

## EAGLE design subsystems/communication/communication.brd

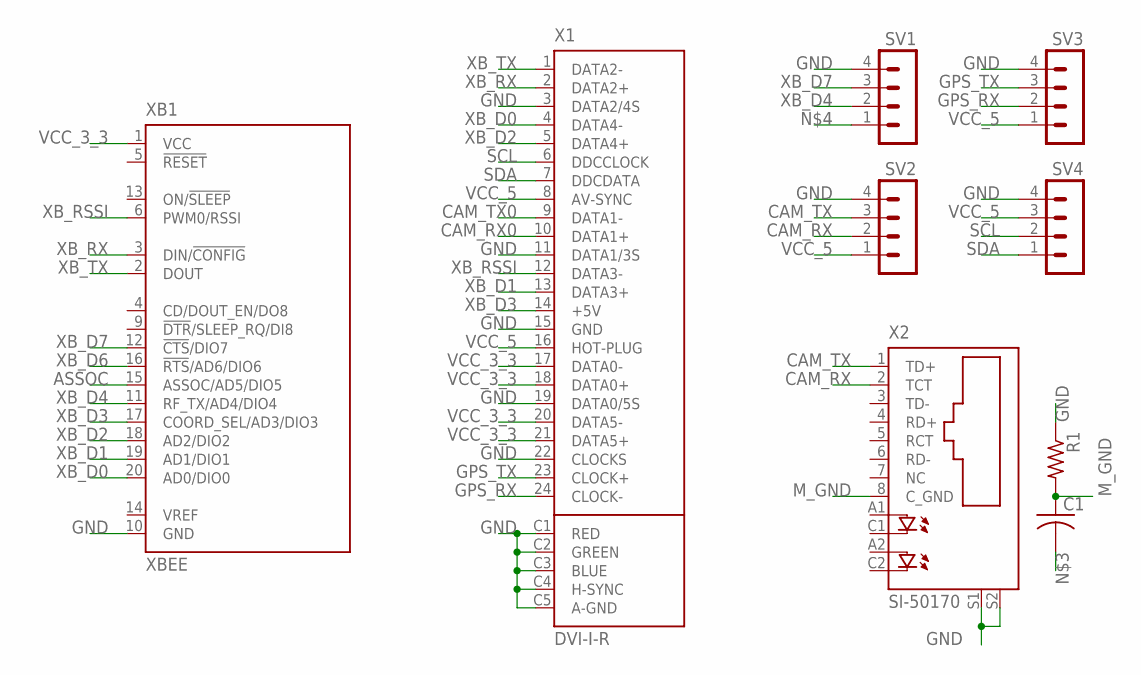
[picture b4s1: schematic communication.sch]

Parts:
C1: C-US025-024X044; C025-024X044
R1: R-US_0204/2V; 0204V
SV1, SV2, SV3, SV4: MA04-1
X1: DVI-I-R
X2: SI-50170
XB1: XBEE

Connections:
AGND: X1.C6 (AGND)
ASSOC: XB1.15 (ASSOC/AD5/DIO5)
CAM_RX: SV2.2, X2.2 (TCT)
CAM_RX0: X1.10 (DATA1+)
CAM_TX: SV2.3, X2.1 (TD+)
CAM_TX0: X1.9 (DATA1-)
GND: R1.1, SV1.4, SV2.4, SV3.4, SV4.4, X1.3 (DATA2/4S), X1.11 (DATA1/3S), X1.15 (GND), X1.19 (DATA0/5S), X1.22 (CLOCKS), X1.C1 (RED), X1.C2 (GREEN), X1.C3 (BLUE), X1.C4 (H-SYNC), X1.C5 (A-GND), X2.S1, X2.S2, XB1.10 (GND)
GPS_RX: SV3.2, X1.24 (CLOCK-)
GPS_TX: SV3.3, X1.23 (CLOCK+)
M_GND: C1.1, R1.2, X2.8 (C_GND)
SCL: SV4.2, X1.6 (DDCCLOCK)
SDA: SV4.1, X1.7 (DDCDATA)
VCC_3_3: X1.17 (DATA0-), X1.18 (DATA0+), X1.20 (DATA5-), X1.21 (DATA5+), XB1.1 (VCC)
VCC_5: SV2.1, SV3.1, SV4.3, X1.8 (AV-SYNC), X1.16 (HOT-PLUG)
XB_D0: X1.4 (DATA4-), XB1.20 (AD0/DIO0)
XB_D1: X1.13 (DATA3+), XB1.19 (AD1/DIO1)
XB_D2: X1.5 (DATA4+), XB1.18 (AD2/DIO2)
XB_D3: X1.14 (+5V), XB1.17 (COORD_SEL/AD3/DIO3)
XB_D4: SV1.2, XB1.11 (RF_TX/AD4/DIO4)
XB_D6: XB1.16 (!RTS!/AD6/DIO6)
XB_D7: SV1.3, XB1.12 (!CTS!/DIO7)
XB_RSSI: X1.12 (DATA3-), XB1.6 (PWM0/RSSI)
XB_RX: X1.2 (DATA2+), XB1.3 (DIN/!CONFIG)
XB_TX: X1.1 (DATA2-), XB1.2 (DOUT)

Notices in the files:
parts and their libraries:
SparkFun-Boards: Licensing: Creative Commons ShareAlike 4.0 International - https://creativecommons.org/licenses/by-sa/4.0
